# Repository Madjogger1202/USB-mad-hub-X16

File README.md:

# USB-mad-hub-X16

> **16-port USB 2.0 hub** on five cascaded **CH334R** controllers, with per-connector current-limited power switches, ESD protection and an external power input.  
> Eight stacked dual USB-A connectors on a 71 × 63 mm two-layer board.

<p align="center"><i>Board preview (connector side / component side) generated from the KiCad board file</i></p>

---

## Overview

One CH334R takes the upstream USB-C port and feeds four more CH334R hubs, each serving four downstream ports — 16 ports in total.  
Downstream power can come either from the upstream USB port or from an external supply on the barrel jack; two slide switches and two **TPS22975** load switches select and enable the downstream rail.

---

## Architecture

```
USB-C (upstream) ──► CH334R ──┬──► CH334R ──► 4× USB-A
                              ├──► CH334R ──► 4× USB-A
                              ├──► CH334R ──► 4× USB-A
                              └──► CH334R ──► 4× USB-A

USB-C 5 V ── SW1 + TPS22975 ──┐
Barrel jack ──────────────────┴── SW2 + TPS22975 ──► downstream 5 V ──► 8× AP2822 ──► USB-A VBUS
```

---

## What's on the board

| Block | Part | Purpose |
|:--|:--|:--|
| Hub controllers | 5× **CH334R** | 4-port USB 2.0 hubs, two-tier tree (1 + 4) |
| Downstream ports | 8× stacked dual USB-A | 16 ports |
| Port power switches | 8× **AP2822** | Current-limited VBUS switch, one per dual connector |
| Rail switches | 2× **TPS22975** + 2× slide switch | Bus-power / external-power selection and downstream power enable |
| ESD / surge protection | 8× **PESD5V0S1BB**, 2× **SMBJ12A** | ESD and surge protection |
| Upstream | USB-C (USB 2.0) | Data and bus power |
| External power | Barrel jack | 5 V supply for the downstream ports |

---

## Specifications

| Parameter | Value |
|:--|:--|
| Ports | 16× USB-A downstream, 1× USB-C upstream |
| USB standard | USB 2.0 |
| Board outline | 71.2 × 63.1 mm |
| Layers | 2 |
| Thickness | 1.6 mm |
| Components | 87 |
| Revision | rev0 |

---

## Repository structure

```
USB mad hub X16.kicad_sch   — schematic
USB mad hub X16.kicad_pcb   — PCB layout
img/                        — board previews
```

---

## Development environment

- **Schematic & PCB:** KiCad 9

---

*by [@madjogger](https://t.me/madjogger)*

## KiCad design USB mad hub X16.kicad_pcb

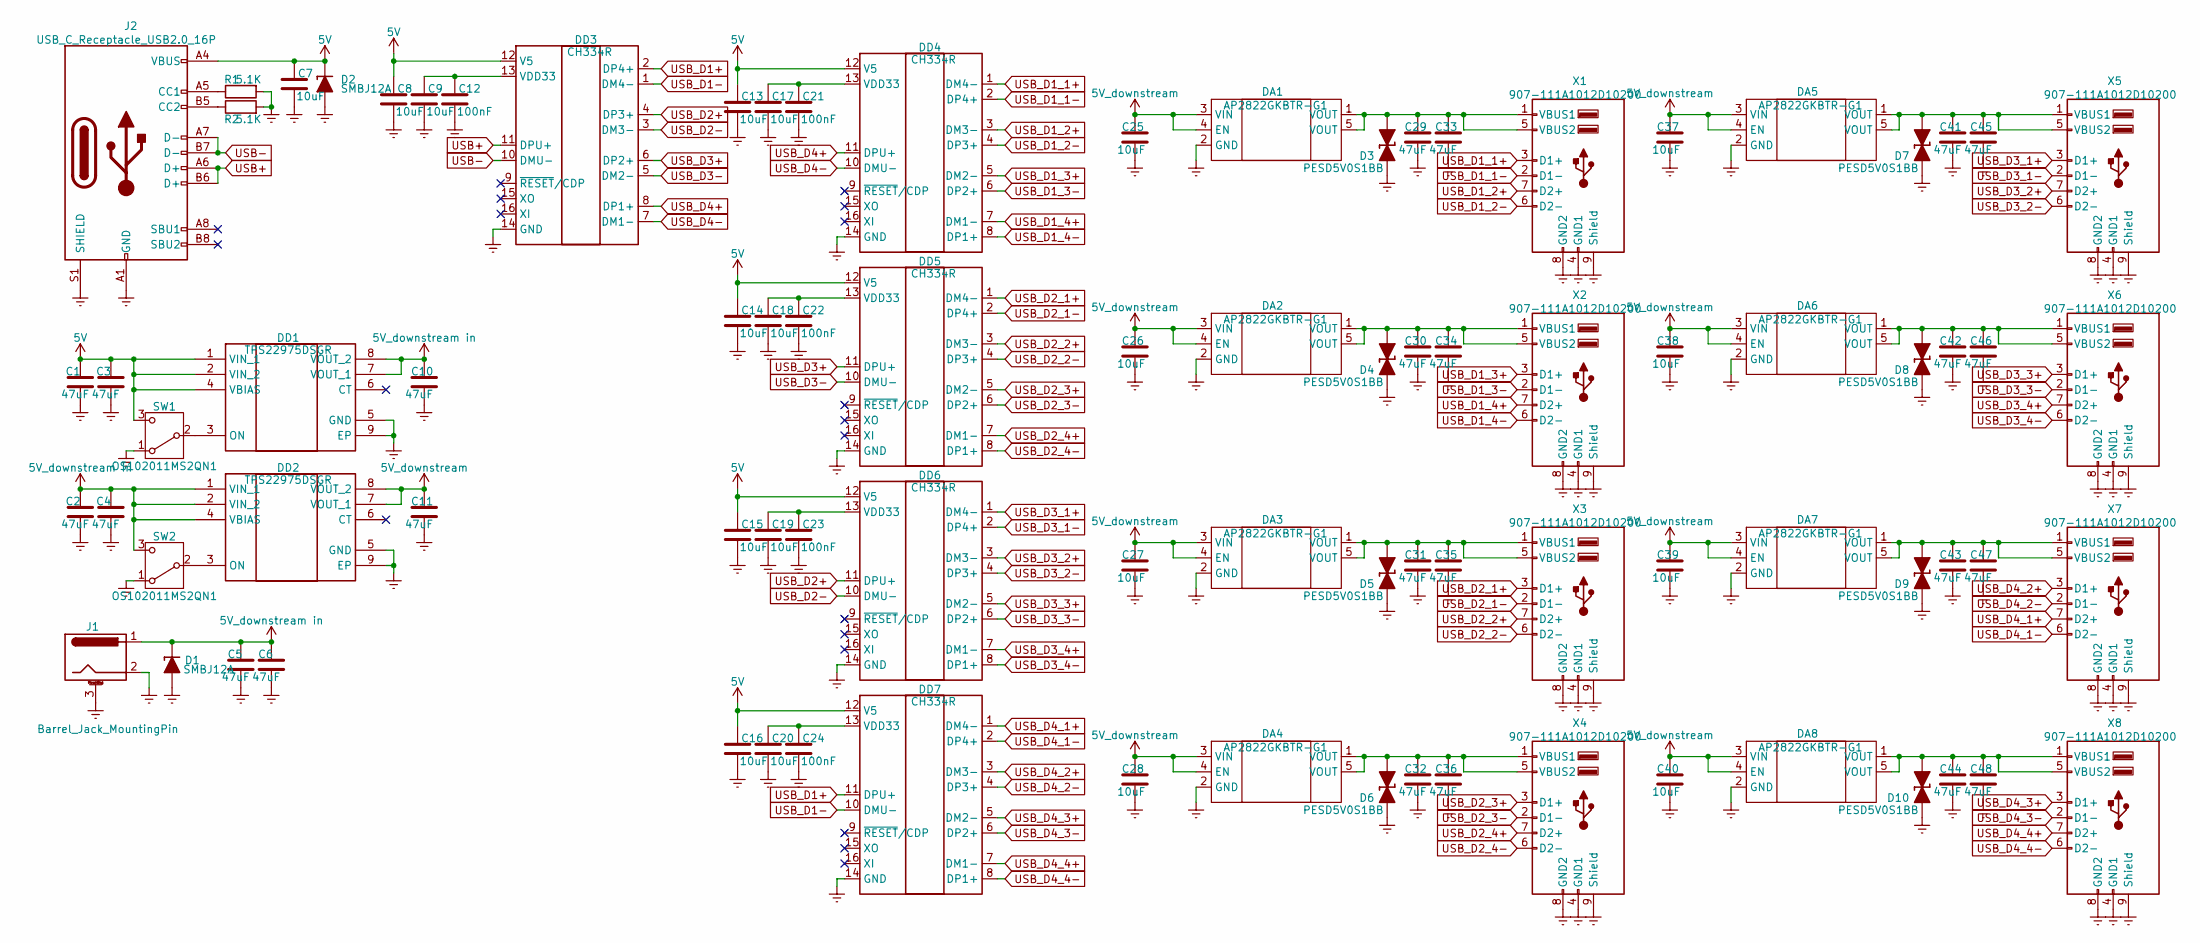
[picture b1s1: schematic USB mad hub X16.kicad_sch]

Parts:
C1, C2, C3, C4, C5, C6, C10, C11, C29, C30, C31, C32, C33, C34, C35, C36, C41, C42, C43, C44, C45, C46, C47, C48: 47uF; C_0603_1608Metric
C7, C8, C9, C13, C14, C15, C16, C17, C18, C19, C20, C25, C26, C27, C28, C37, C38, C39, C40: 10uF; C_0402_1005Metric
C12, C21, C22, C23, C24: 100nF; C_0402_1005Metric
D1, D2: SMBJ12A; D_SMB
D3, D4, D5, D6, D7, D8, D9, D10: PESD5V0S1BB; D_SOD-523_TVS
DA1, DA2, DA3, DA4, DA5, DA6, DA7, DA8: AP2822GKBTR-G1; SOT-23-5
DD1, DD2: TPS22975DSGR; Manufacturer_Part_Number TPS22975DSGR; Mouser Part Number 595-TPS22975DSGR
DD3, DD4, DD5, DD6, DD7: CH334R; QSOP-16_3.9x4.9mm_P0.635mm
J1: Barrel_Jack_MountingPin; BarrelJack_GCT_DCJ200-10-A_Horizontal
J2: USB_C_Receptacle_USB2.0_16P; USB_C_Receptacle_GCT_USB4105-xx-A_16P_TopMnt_Horizontal
R1, R2: 5.1K; R_0402_1005Metric
SW1, SW2: OS102011MS2QN1; SW_Slide_SPDT_Straight_CK_OS102011MS2Q
X1, X2, X3, X4, X5, X6, X7, X8: 907-111A1012D10200; USB_A_CUI_UJ2-ADH-TH_Horizontal_Stacked

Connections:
5V: C1.1, C3.1, C7.1, C8.1, C13.1, C14.1, C15.1, C16.1, D2.1 (K), DD1.1 (VIN_1), DD1.2 (VIN_2), DD1.4 (VBIAS), DD3.12 (V5), DD4.12 (V5), DD5.12 (V5), DD6.12 (V5), DD7.12 (V5), J2.A4 (VBUS), J2.A9 (VBUS), J2.B4 (VBUS), J2.B9 (VBUS), SW1.3 (C)
5V_downstream: C11.1, C25.1, C26.1, C27.1, C28.1, C37.1, C38.1, C39.1, C40.1, DA1.3 (VIN), DA1.4 (EN), DA2.3 (VIN), DA2.4 (EN), DA3.3 (VIN), DA3.4 (EN), DA4.3 (VIN), DA4.4 (EN), DA5.3 (VIN), DA5.4 (EN), DA6.3 (VIN), DA6.4 (EN), DA7.3 (VIN), DA7.4 (EN), DA8.3 (VIN), DA8.4 (EN), DD2.7 (VOUT_1), DD2.8 (VOUT_2)
5V_downstream in: C2.1, C4.1, C5.1, C6.1, C10.1, D1.1 (K), DD1.7 (VOUT_1), DD1.8 (VOUT_2), DD2.1 (VIN_1), DD2.2 (VIN_2), DD2.4 (VBIAS), J1.1, SW2.3 (C)
Earth: C1.2, C2.2, C3.2, C4.2, C5.2, C6.2, C7.2, C8.2, C9.2, C10.2, C11.2, C12.2, C13.2, C14.2, C15.2, C16.2, C17.2, C18.2, C19.2, C20.2, C21.2, C22.2, C23.2, C24.2, C25.2, C26.2, C27.2, C28.2, C29.2, C30.2, C31.2, C32.2, C33.2, C34.2, C35.2, C36.2, C37.2, C38.2, C39.2, C40.2, C41.2, C42.2, C43.2, C44.2, C45.2, C46.2, C47.2, C48.2, D1.2 (A), D2.2 (A), D3.1 (K), D4.1 (K), D5.1 (K), D6.1 (K), D7.1 (K), D8.1 (K), D9.1 (K), D10.1 (K), DA1.2 (GND), DA2.2 (GND), DA3.2 (GND), DA4.2 (GND), DA5.2 (GND), DA6.2 (GND), DA7.2 (GND), DA8.2 (GND), DD1.5 (GND), DD1.9 (EP), DD2.5 (GND), DD2.9 (EP), DD3.14 (GND), DD4.14 (GND), DD5.14 (GND), DD6.14 (GND), DD7.14 (GND), J1.2, J1.3 (MountPin), J2.A1 (GND), J2.A12 (GND), J2.B1 (GND), J2.B12 (GND), J2.S1 (SHIELD), R1.2, R2.2, SW1.1 (A), SW2.1 (A), X1.4 (GND1), X1.8 (GND2), X1.9 (Shield), X2.4 (GND1), X2.8 (GND2), X2.9 (Shield), X3.4 (GND1), X3.8 (GND2), X3.9 (Shield), X4.4 (GND1), X4.8 (GND2), X4.9 (Shield), X5.4 (GND1), X5.8 (GND2), X5.9 (Shield), X6.4 (GND1), X6.8 (GND2), X6.9 (Shield), X7.4 (GND1), X7.8 (GND2), X7.9 (Shield), X8.4 (GND1), X8.8 (GND2), X8.9 (Shield)
unnamed: C29.1, C33.1, D3.2 (A), DA1.1 (VOUT), DA1.5 (VOUT), X1.1 (VBUS1), X1.5 (VBUS2)
unnamed: C30.1, C34.1, D4.2 (A), DA2.1 (VOUT), DA2.5 (VOUT), X2.1 (VBUS1), X2.5 (VBUS2)
unnamed: C31.1, C35.1, D5.2 (A), DA3.1 (VOUT), DA3.5 (VOUT), X3.1 (VBUS1), X3.5 (VBUS2)
unnamed: C32.1, C36.1, D6.2 (A), DA4.1 (VOUT), DA4.5 (VOUT), X4.1 (VBUS1), X4.5 (VBUS2)
unnamed: C41.1, C45.1, D7.2 (A), DA5.1 (VOUT), DA5.5 (VOUT), X5.1 (VBUS1), X5.5 (VBUS2)
unnamed: C42.1, C46.1, D8.2 (A), DA6.1 (VOUT), DA6.5 (VOUT), X6.1 (VBUS1), X6.5 (VBUS2)
unnamed: C43.1, C47.1, D9.2 (A), DA7.1 (VOUT), DA7.5 (VOUT), X7.1 (VBUS1), X7.5 (VBUS2)
unnamed: C44.1, C48.1, D10.2 (A), DA8.1 (VOUT), DA8.5 (VOUT), X8.1 (VBUS1), X8.5 (VBUS2)
unnamed: DD1.3 (ON), SW1.2 (B)
unnamed: DD2.3 (ON), SW2.2 (B)
unnamed: C9.1, C12.1, DD3.13 (VDD33)
unnamed: C17.1, C21.1, DD4.13 (VDD33)
unnamed: C18.1, C22.1, DD5.13 (VDD33)
unnamed: C19.1, C23.1, DD6.13 (VDD33)
unnamed: C20.1, C24.1, DD7.13 (VDD33)
unnamed: J2.A5 (CC1), R1.1
unnamed: J2.B5 (CC2), R2.1
USB+: DD3.11 (DPU+), J2.A6 (D+), J2.B6 (D+)
USB-: DD3.10 (DMU-), J2.A7 (D-), J2.B7 (D-)
USB_D1+: DD3.2 (DP4+), DD7.11 (DPU+)
USB_D1-: DD3.1 (DM4-), DD7.10 (DMU-)
USB_D1_1+: DD4.1 (DM4-), X1.3 (D1+)
USB_D1_1-: DD4.2 (DP4+), X1.2 (D1-)
USB_D1_2+: DD4.3 (DM3-), X1.7 (D2+)
USB_D1_2-: DD4.4 (DP3+), X1.6 (D2-)
USB_D1_3+: DD4.5 (DM2-), X2.3 (D1+)
USB_D1_3-: DD4.6 (DP2+), X2.2 (D1-)
USB_D1_4+: DD4.7 (DM1-), X2.7 (D2+)
USB_D1_4-: DD4.8 (DP1+), X2.6 (D2-)
USB_D2+: DD3.4 (DP3+), DD6.11 (DPU+)
USB_D2-: DD3.3 (DM3-), DD6.10 (DMU-)
USB_D2_1+: DD5.1 (DM4-), X3.3 (D1+)
USB_D2_1-: DD5.2 (DP4+), X3.2 (D1-)
USB_D2_2+: DD5.3 (DM3-), X3.7 (D2+)
USB_D2_2-: DD5.4 (DP3+), X3.6 (D2-)
USB_D2_3+: DD5.5 (DM2-), X4.3 (D1+)
USB_D2_3-: DD5.6 (DP2+), X4.2 (D1-)
USB_D2_4+: DD5.7 (DM1-), X4.7 (D2+)
USB_D2_4-: DD5.8 (DP1+), X4.6 (D2-)
USB_D3+: DD3.6 (DP2+), DD5.11 (DPU+)
USB_D3-: DD3.5 (DM2-), DD5.10 (DMU-)
USB_D3_1+: DD6.1 (DM4-), X5.3 (D1+)
USB_D3_1-: DD6.2 (DP4+), X5.2 (D1-)
USB_D3_2+: DD6.3 (DM3-), X5.7 (D2+)
USB_D3_2-: DD6.4 (DP3+), X5.6 (D2-)
USB_D3_3+: DD6.5 (DM2-), X6.3 (D1+)
USB_D3_3-: DD6.6 (DP2+), X6.2 (D1-)
USB_D3_4+: DD6.7 (DM1-), X6.7 (D2+)
USB_D3_4-: DD6.8 (DP1+), X6.6 (D2-)
USB_D4+: DD3.8 (DP1+), DD4.11 (DPU+)
USB_D4-: DD3.7 (DM1-), DD4.10 (DMU-)
USB_D4_1+: DD7.1 (DM4-), X7.7 (D2+)
USB_D4_1-: DD7.2 (DP4+), X7.6 (D2-)
USB_D4_2+: DD7.3 (DM3-), X7.3 (D1+)
USB_D4_2-: DD7.4 (DP3+), X7.2 (D1-)
USB_D4_3+: DD7.5 (DM2-), X8.3 (D1+)
USB_D4_3-: DD7.6 (DP2+), X8.2 (D1-)
USB_D4_4+: DD7.7 (DM1-), X8.7 (D2+)
USB_D4_4-: DD7.8 (DP1+), X8.6 (D2-)

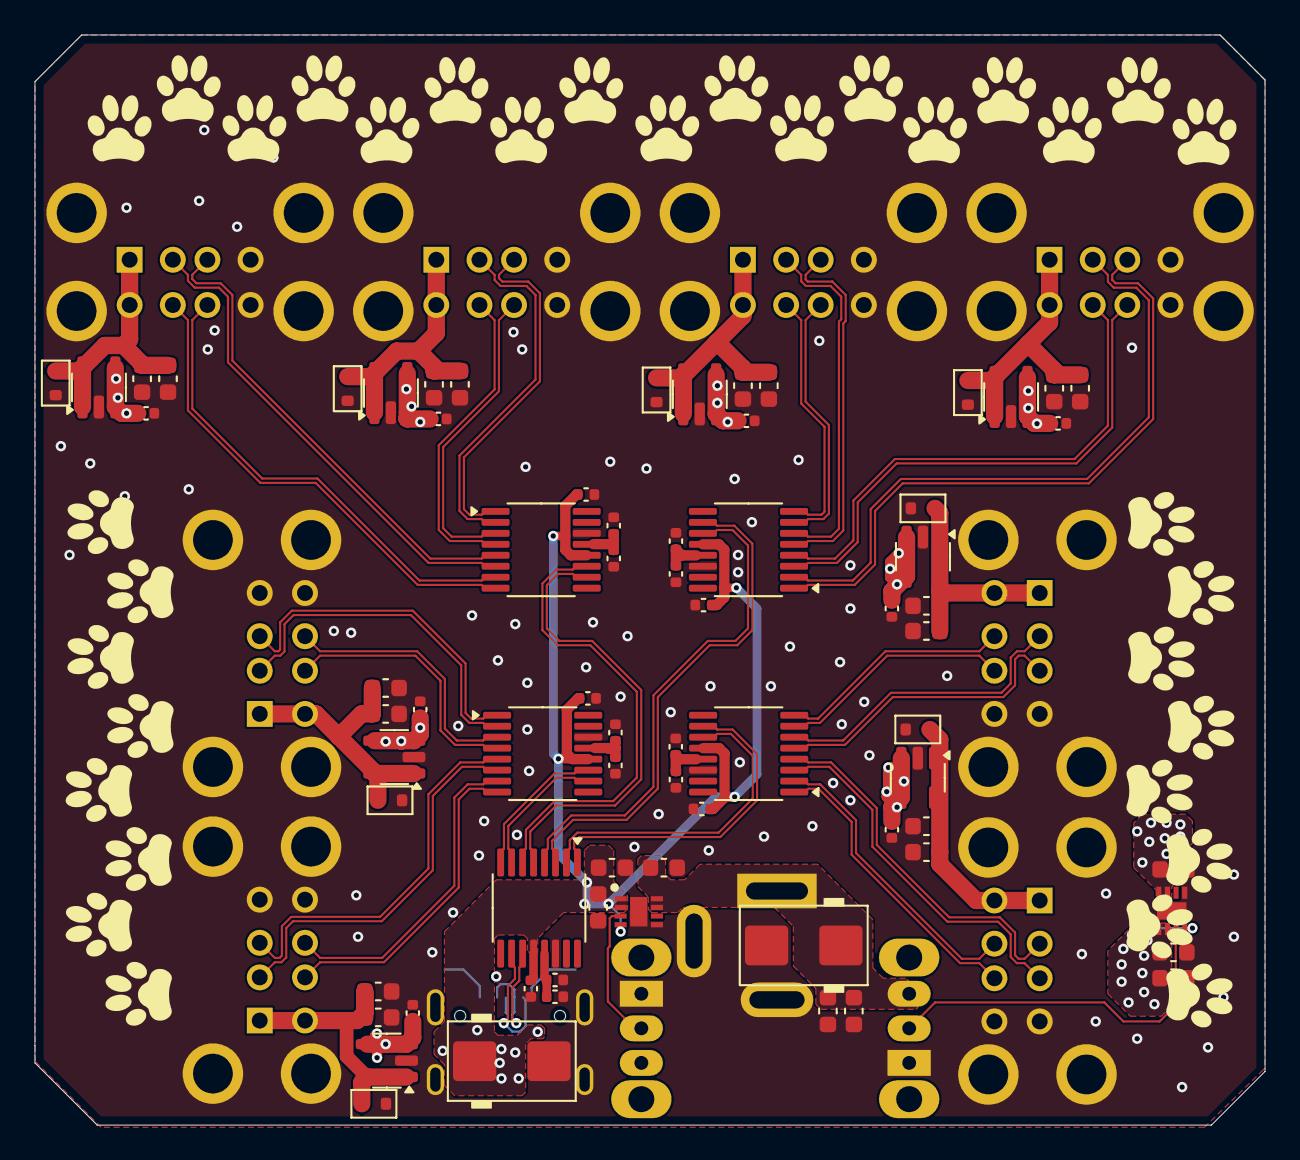
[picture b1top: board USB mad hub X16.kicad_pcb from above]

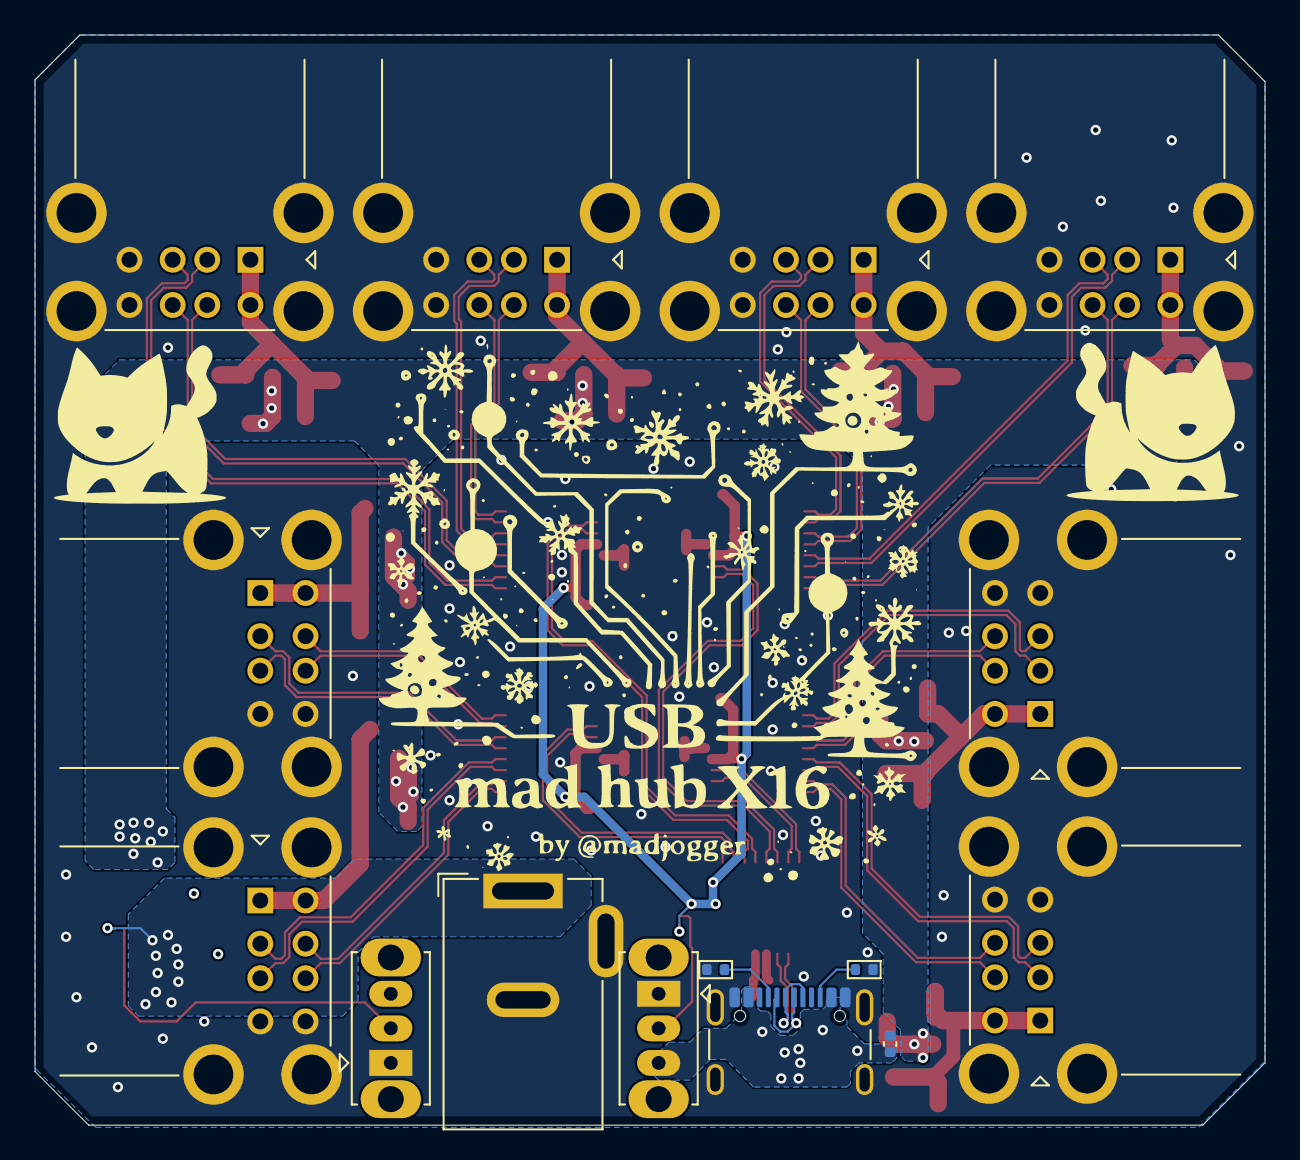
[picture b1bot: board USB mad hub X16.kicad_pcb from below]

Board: 2 copper layers, 71.2 x 63.1 mm, 87 parts (15 on the bottom side), 63 nets.

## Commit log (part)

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2025-12-29 rev0 ready
